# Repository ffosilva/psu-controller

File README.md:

# ATX Power Supply Controller (`psu-controller`)

[-brightgreen)](#pcb-layout--manufacturing-specs)

A discrete, analog hardware controller designed to sequence and manage standard ATX power supplies for non-standard motherboards, repurposed compute platforms (such as the AMD BC-250 mining board), single-board computers, and custom electronics fixtures.

---

## 📖 Table of Contents

- [Motivation & Problem Solved](#-motivation--problem-solved)
- [Key Features](#-key-features)
- [System Architecture](#-system-architecture)
- [Theory of Operation](#-theory-of-operation)
- [Header Pinout & Wiring](#-header-pinout--wiring)
- [Bill of Materials (BOM)](#-bill-of-materials-bom)
- [PCB Layout & Manufacturing Specs](#-pcb-layout--manufacturing-specs)
- [Bench Testing & Verification](#-bench-testing--verification)
- [Host BIOS Configuration](#-host-bios-configuration)
- [Repository Structure](#-repository-structure)
- [Documentation Index](#-documentation-index)
- [License](#-license)

---

## ⚡ Motivation & Problem Solved

Repurposed compute hardware (such as headless crypto-mining boards like the AMD BC-250, embedded industrial boards, and retro computing conversions) often lack standard front-panel ATX power management circuits. 

Without a dedicated controller:
1. **The Green Wire Hack:** Operators typically short the ATX `PS_ON#` wire (green) to Ground (black) with a jumper clip or switch.
2. **24/7 Power Waste & Wear:** The power supply and all chassis fans remain powered continuously at high wattage—even after the operating system cleanly halts and unmounts disks.
3. **Loss of ACPI Control:** Pressing a chassis button cannot trigger an ACPI graceful shutdown, risking filesystem corruption.

The **ATX Power Supply Controller** eliminates jumpers by providing an intelligent, fully autonomous, discrete hardware sequency bridge between any ATX power supply, the host motherboard, and your chassis buttons/LEDs.

---

## ✨ Key Features

- **Cold Boot RC Sequencing:** Momentary chassis button tap charges a timing capacitor ($C_{hold} = 22\ \mu\text{F}$ via $R_{bleed} = 120\text{ k}\Omega$), asserting ATX `PS_ON#` for ~3.5 seconds to allow the host to spin up.
- **Active Telemetry Latching:** Continuously monitors host power state via a 3.3V telemetry pin (e.g., TPM header pin `HOST_ON`). Once booted, host voltage locks `PS_ON#` low indefinitely.
- **Safe ACPI Button Mirroring:** Routes button pulses to the host's power button pad (`BTN_OUT`) through an open-drain N-channel MOSFET (`2N7000`), allowing:
  - **Short tap (200 ms):** Graceful OS ACPI shutdown without dropping ATX main power prematurely.
  - **Long press (4.0 seconds):** Hardware-level emergency forced power cut when OS kernel freezes.
- **Automated Standby Transition:** When the operating system finishes shutting down, `HOST_ON` drops to 0V. The controller de-asserts `PS_ON#` within 300 ms, putting the ATX power supply back into standby ($< 50\ \mu\text{A}$ quiescent draw).
- **Remote Microcontroller Wake (`ESP_WAKE`):** Accepts a 3.3V logic pulse from an ESP32, ESP8266, or Raspberry Pi Pico to power on the system remotely over WiFi/Bluetooth.
- **Hardware Remote Inhibit:** Uses an NPN transistor clamp to hardware-shunt `ESP_WAKE` directly to ground whenever the system is running, preventing accidental resets or wake loops.
- **Chassis Power LED Driver:** Built-in low-side switched driver (~15 mA) indicates true host system state.
- **100% Discrete Through-Hole Parts:** Built entirely with cheap, universally available "jellybean" components (TO-92 transistors, axial 1/4W resistors, DO-41 diodes, radial capacitors).
- **DIY Single-Sided PCB Design:** 1-layer bottom copper routing (`B.Cu` only, zero vias, zero top-side copper traces) designed specifically for home etching (toner transfer / photoresist) or desktop CNC milling.

---

## 🏗 System Architecture

```text
+---------------------+               +-----------------------+
|   Chassis Front     |               |    ATX Power Supply   |
|       Panel         |               |      (24-Pin Main)    |
|                     |               |                       |
| [Power Button]      |               |  Pin 9  (+5VSB, Purp) |
| [Power LED Ring]    |               |  Pin 16 (PS_ON#, Grn) |
|                     |               |  Pin 3  (GND, Blk)    |
+----------+----------+               +-----------+-----------+
           |                                      |
           | 4 wires                              | 3 wires
           v                                      v
     +-----+--------------------------------------+-----+
     |                                                  |
     |         ATX POWER SUPPLY CONTROLLER PCB          |
     |          (55 mm x 45 mm Single-Sided)            |
     |                                                  |
     +-----+--------------------------------------+-----+
           ^                                      ^
           | 2-3 wires                            | 2 wires
           |                                      |
+----------+----------+               +-----------+-----------+
| ESP32 / ESP8266     |               |   Host Motherboard    |
| Microcontroller     |               |     (AMD BC-250)      |
|                     |               |                       |
| - 5V / VIN (Power)  |               | - TPMS1 Pin 1 (3.3V)  |
| - WAKE (GPIO Out)   |               | - PWR_BTN# Solder Pad |
| - GND (Common)      |               | - Common Ground       |
+---------------------+               +-----------------------+
```

---

## 🔬 Theory of Operation

```text
========================================================================================
                          CIRCUIT SCHEMATIC OVERVIEW
========================================================================================

                                  +5VSB (J1 Pin 1, ATX Pin 9)
                                       |
                +----------------------+-------------------------------+
                |                      |                               |
            [R1: 10k]             Source [Q1: BS250]               [R_led: 330R]
                |                    (P-Ch MOSFET)                     |
  BTN_IN -------+------------------+ Gate                              v Anode
  (J3 Pin 1)    |                      | Drain                      [Power LED]
             [C_deb: 100nF]        [D2: 1N5819]                     (J4 Pin 1)
                |                      |                               | Cathode
  GND ----------+                      v                               (J4 Pin 2)
                                 Node [V_GATE]                         |
  HOST_ON (3.3V TPM) -----[D1: 1N5819]-+                               |
  (J2 Pin 1)                           |                               |
                                       |                               |
  ESP_WAKE (3.3V) ----[R5: 1k]---------+-----[D3: 1N5819]--+          |
  (J5 Pin 2)          |                                    |          |
                   Collector                               v          |
                      |                             +-------------+   |
  HOST_ON ---[R6: 10k]+ Base [Q5: 2N3904]           | [C_hold]    |   |
  (Inhibit)           | (Inhibit Switch)            | (22uF)      |   |
                   Emitter                          | [R_bleed]   |   |
                      |                             | (120k)      |   |
                     GND                            +------+------+   |
                                                           |          |
                                                          GND         |
                                                                    Gate
                                                                      v
                                                             +-----------------+
                                                             | Q2: 2N7000      |
                                ATX PS_ON# <-----------------+ (N-Ch MOSFET)   |
                                (J1 Pin 2, ATX Pin 16)       | Source          |
                                                             +--------+--------+
                                                                      |
                                                                     GND

  Q1 Drain (5V Pulse) --------[R2: 1k]-------------> Gate (Q3: 2N7000) -> BTN_OUT (J2.2)
  HOST_ON (3.3V TPM) ---------[R4: 4.7k]-----------> Base (Q4: 2N3904) -> LED- (J4.2)
========================================================================================
```

1. **Standby (Off):** ATX mains is plugged in. `+5VSB` is active. Node `V_GATE` is 0V, $Q_2$ is OFF, `PS_ON#` floats at 5V, power draw is $< 50\ \mu\text{A}$.
2. **Cold Power-On:** Pressing the chassis button pulls $Q_1$ gate low, turning $Q_1$ ON. A 5V pulse charges $C_{hold}$ ($22\ \mu\text{F}$) through Schottky diode $D_2$ in $< 2\text{ ms}$, immediately turning ON $Q_2$ and pulling `PS_ON#` to GND.
3. **Hold-Up Timer:** Once released, $C_{hold}$ discharges through $R_{bleed}$ ($120\text{ k}\Omega$). $Q_2$ remains fully saturated for ~3.5 seconds, giving the host ample time to power on and initialize.
4. **Active Latching:** As the host boots, its 3.3V TPM header asserts `HOST_ON`. Diode $D_1$ conducts, locking `V_GATE` to ~3.05V indefinitely.
5. **ACPI Button Mirroring:** While running, pressing the front panel button turns on $Q_3$, pulling the motherboard power pad (`BTN_OUT`) to ground. The OS registers the ACPI event and initiates a clean shutdown. `PS_ON#` stays grounded by `HOST_ON` during shutdown.
6. **Graceful Power Cut:** When the OS halts, the motherboard turns off and `HOST_ON` drops to 0V. $D_1$ stops conducting, $C_{hold}$ discharges in ~300 ms, $Q_2$ turns off, and the ATX supply turns off main rails.
7. **Emergency 4-Second Override:** If the OS freezes, holding the button for 4.0 seconds holds `BTN_OUT` low, triggering the motherboard hardware supervisor force-off.
8. **Remote Wake & Hardware Inhibit:** A 3.3V pulse on `ESP_WAKE` charges $C_{hold}$ via $D_3$, turning on the PSU. When the host is already running, $Q_5$ clamps the wake input directly to GND, preventing unexpected glitches.

---

## 🔌 Header Pinout & Wiring

| Header | Pin | Signal | Target Connection | Description |
| :--- | :--- | :--- | :--- | :--- |
| **J1: ATX PSU** | 1 | `+5VSB` | ATX 24-Pin Pin 9 (Purple) | Standby +5V DC power |
| | 2 | `PS_ON#` | ATX 24-Pin Pin 16 (Green) | Active-low main rail enable |
| | 3 | `GND` | ATX 24-Pin Pin 3/5/7/15/17 (Black) | Common system ground return |
| **J2: Host Board** | 1 | `HOST_ON` | Motherboard TPM Header Pin 1 (3.3V) | Active power telemetry sense line |
| | 2 | `BTN_OUT` | Motherboard `PWR_BTN#` Solder Pad | Open-drain ACPI button pulse output |
| **J3: Chassis Button**| 1 | `BTN_IN` | Pushbutton Terminal 1 | Momentary switch active-low input |
| | 2 | `GND` | Pushbutton Terminal 2 | Switch ground return |
| **J4: Power LED** | 1 | `LED+` | Power LED Anode (+) | +5V DC current-limited via onboard 330Ω |
| | 2 | `LED-` | Power LED Cathode (-) | Low-side switched ground via $Q_4$ |
| **J5: Remote MCU** | 1 | `+5VSB` | ESP32 `VIN` / `5V` | Standby power for external MCU |
| | 2 | `ESP_WAKE`| ESP32 GPIO (Output) | Remote wake active-high (3.3V) pulse |
| | 3 | `GND` | ESP32 `GND` | Shared ground return |

> [!TIP]
> Use an ATX 24-pin extension cable to tap Pin 9 (`+5VSB`), Pin 16 (`PS_ON#`), and Ground without altering or cutting your power supply harness.

For full pinouts, motherboard solder points, and step-by-step assembly advice, see [docs/wiring-guide.md](docs/wiring-guide.md).

---

## 📦 Bill of Materials (BOM)

All components are standard through-hole parts with wide global availability:

| Ref | Qty | Part / Value | Description | Package | Example MPN |
| :--- | :--- | :--- | :--- | :--- | :--- |
| **Q1** | 1 | BS250 | P-Channel Logic MOSFET (-45V, 180mA) | TO-92 | `BS250P` (or 2N3906 PNP) |
| **Q2, Q3** | 2 | 2N7000 | N-Channel Logic MOSFET (60V, 200mA) | TO-92 | `2N7000` |
| **Q4, Q5** | 2 | 2N3904 | NPN General Purpose BJT (40V, 200mA) | TO-92 | `2N3904` |
| **D1, D2, D3** | 3 | 1N5819 | Schottky Barrier Diode (40V, 1A, $V_F \approx 0.25\text{V}$) | DO-41 Axial | `1N5819` |
| **C_hold** | 1 | 22 µF, 25V | Radial Aluminum Electrolytic Capacitor | Radial Ø5mm | `ECA-1EHG220` |
| **C_deb, C_byp**| 2 | 100 nF (0.1 µF) | Multilayer Ceramic Capacitor (50V) | Radial 2.54mm | `C315C104K5R5TA` |
| **R1, R6** | 2 | 10 kΩ, 1/4W | Metal / Carbon Film Resistor (5%) | Axial 7.62mm | `CFR-25JB-52-10K` |
| **R2, R5** | 2 | 1 kΩ, 1/4W | Metal / Carbon Film Resistor (5%) | Axial 7.62mm | `CFR-25JB-52-1K` |
| **R4** | 1 | 4.7 kΩ, 1/4W | Metal / Carbon Film Resistor (5%) | Axial 7.62mm | `CFR-25JB-52-4K7` |
| **R_bleed** | 1 | 120 kΩ, 1/4W | Metal / Carbon Film Resistor (5%) | Axial 7.62mm | `CFR-25JB-52-120K` |
| **R_led** | 1 | 330 Ω, 1/4W | Metal / Carbon Film Resistor (5%) | Axial 7.62mm | `CFR-25JB-52-330R` |
| **J1, J5** | 2 | 3-Pin Header | 2.54mm (0.1") Male Pin Header | 1x03 THT | Standard 2.54mm Header |
| **J2, J3, J4** | 3 | 2-Pin Header | 2.54mm (0.1") Male Pin Header | 1x02 THT | Standard 2.54mm Header |

For detailed component substitutions, pinouts, and purchasing links, see [docs/bom.md](docs/bom.md).

---

## 🛠 PCB Layout & Manufacturing Specs

The PCB is built in KiCad 8 as a **true single-sided layout**:
- **Board Dimensions:** $55.0\text{ mm} \times 45.0\text{ mm}$
- **Layer Stackup:** 1-Layer Copper (`B.Cu` bottom solder side only). Zero copper traces on `F.Cu`, zero vias.
- **Top-Side Crossover Strategy:** Resistor `R2` ($10.16\text{ mm}$ axial span) and diode `D1` ($7.62\text{ mm}$ axial span) act as natural component bridges across bottom copper traces on `B.Cu`, avoiding the need for wire jumpers.
- **DIY Etch / Desktop CNC Milling Tolerances:**
  - Power / Ground Traces: `0.80 mm`
  - Signal Traces: `0.60 mm`
  - Minimum Copper Clearance: $\ge 0.45\text{ mm}$
  - Component Pads: `1.80 mm` outer diameter (`0.8 mm` drill)
  - Connector Pads: `2.00 mm` outer diameter (`1.0 mm` drill)
  - Expanded TO-92 Footprints: $\ge 2.54\text{ mm}$ lead spread for easy hand soldering and generous isolation.

### Manufacturing Files (`kicad/gerbers/`)
- `atx-psu-controller-B_Cu.gbr` — Bottom copper layer (traces & ground plane)
- `atx-psu-controller-B_Mask.gbr` — Solder mask (bottom)
- `atx-psu-controller-F_SilkS.gbr` — Top silkscreen (component placement & polarity)
- `atx-psu-controller-Edge_Cuts.gbr` — Board outline
- `atx-psu-controller-PTH.drl` — Excellon drill file (component holes only, no via drills)

---

## 🧪 Bench Testing & Verification

Before installing into your system, complete bench verification using a DC power supply and multimeter:

1. **Pre-Power Continuity Check:** Measure resistance between `+5VSB` and `GND` ($> 100\text{ k}\Omega$), and between `PS_ON#` and `GND` ($> 1\text{ M}\Omega$).
2. **Standby Current Draw:** Apply 5.0V to `J1.1`. Quiescent current must measure $< 50\ \mu\text{A}$ (typically $\sim 12\ \mu\text{A}$).
3. **Cold Boot Hold-Up Time:** Tap `BTN_IN` to `GND`. `PS_ON#` drops to $< 0.1\text{V}$ instantly and remains low for $2.5\text{s}$ to $3.5\text{s}$ before releasing.
4. **Telemetry Latch:** Apply 3.3V to `HOST_ON` within 2 seconds of button press. `PS_ON#` stays latched low indefinitely; the status LED lights up.
5. **ACPI Button Mirroring:** Tap `BTN_IN`. `BTN_OUT` pulses low ($< 0.1\text{V}$) while `PS_ON#` remains held low without interruption.
6. **Graceful Shutdown:** Remove 3.3V from `HOST_ON`. `PS_ON#` releases within 300 ms, and the LED turns off.
7. **Remote Wake & Inhibit:** 3.3V pulse on `ESP_WAKE` starts the PSU. When `HOST_ON` is 3.3V, `ESP_WAKE` is clamped to ground by $Q_5$.

For full testing protocols and verification logs, see [docs/testing.md](docs/testing.md).

---

## ⚙ Host BIOS Configuration

To take full advantage of automated cold-boot sequencing:
1. Enter your motherboard BIOS setup during boot (`DEL` or `F2`).
2. Go to **Advanced $\rightarrow$ ACPI Configuration / Power Management**.
3. Set **"Restore on AC Power Loss"** (or **"State After G3"**) to **`Power On`** (or **`Always On`**).
4. Save and exit (`F10`).

The host motherboard will now automatically boot the moment the ATX controller supplies +12V power!

---

## 📁 Repository Structure

```text
psu-controller/
├── docs/
│   ├── schematic.md         # Full ASCII schematic, netlist & circuit theory
│   ├── bom.md               # Complete Bill of Materials, footprints & substitutions
│   ├── wiring-guide.md      # Pinout, cable harnesses & motherboard solder points
│   ├── testing.md           # Bench test protocol, checklist & measurements
│   └── circuit-ideas.md     # Reference comparison (555 timers, flip-flops, latches)
├── kicad/
│   ├── atx-psu-controller.kicad_pro   # KiCad 8 project file
│   ├── atx-psu-controller.kicad_sch   # KiCad schematic
│   ├── atx-psu-controller.kicad_pcb   # KiCad single-sided PCB layout
│   └── gerbers/                       # Gerber RS-274X & Excellon drill files
├── openspec/
│   ├── config.yaml          # OpenSpec workspace configuration
│   ├── specs/               # Active system specifications
│   │   ├── atx-power-control/spec.md
│   │   └── pcb-layout/spec.md
│   └── changes/archive/     # Archived design proposals and implementation tasks
└── README.md                # Project documentation and user guide
```

---

## 📚 Documentation Index

- [Circuit Schematic & Netlist](docs/schematic.md)
- [Bill of Materials & Component Substitutions](docs/bom.md)
- [Hardware Wiring & Integration Guide](docs/wiring-guide.md)
- [Bench Testing & Verification Protocol](docs/testing.md)
- [Circuit Topology Research & Comparison](docs/circuit-ideas.md)
- [OpenSpec: ATX Power Control Spec](openspec/specs/atx-power-control/spec.md)
- [OpenSpec: PCB Layout Spec](openspec/specs/pcb-layout/spec.md)

---

## 📄 License

This hardware project is open-source and released under the [MIT License](LICENSE).

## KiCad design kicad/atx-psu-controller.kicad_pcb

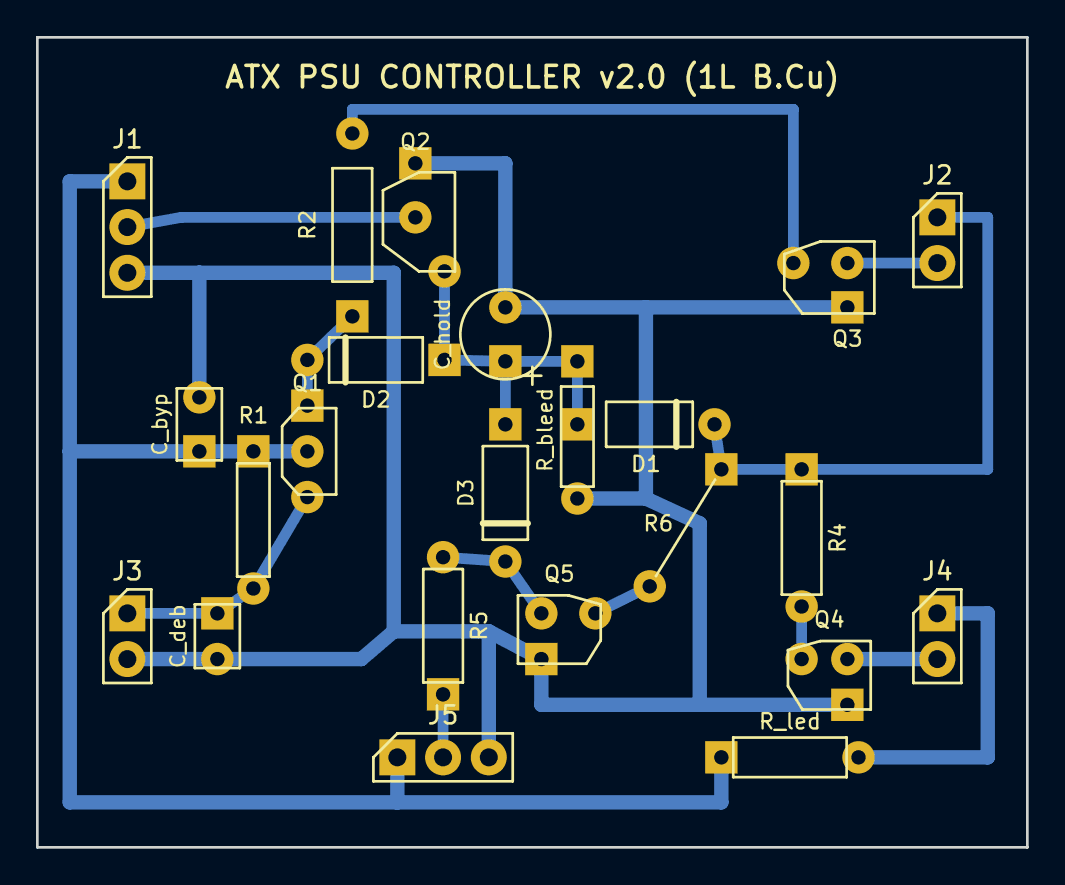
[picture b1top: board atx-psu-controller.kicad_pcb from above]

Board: 2 copper layers, 55.0 x 45.0 mm, 23 parts (0 on the bottom side), 15 nets.

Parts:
C_byp: 100nF; C_Disc_D5.0mm_W2.5mm_P2.54mm
C_deb: 100nF; C_Disc_D5.0mm_W2.5mm_P2.54mm
C_hold: 22uF; CP_Radial_D5.0mm_P2.50mm
D1, D2, D3: 1N5819; D_DO-41_SOD81_P7.62mm_Horizontal
J1: ATX_PSU; PinHeader_1x03_P2.54mm_Vertical
J2: HOST_BC250; PinHeader_1x02_P2.54mm_Vertical
J3: CHASSIS_BTN; PinHeader_1x02_P2.54mm_Vertical
J4: PWR_LED; PinHeader_1x02_P2.54mm_Vertical
J5: ESP_WAKE_HDR; PinHeader_1x03_P2.54mm_Vertical
Q1: BS250; TO-92_HandSolder
Q2, Q3: 2N7000; TO-92_HandSolder
Q4, Q5: 2N3904; TO-92_HandSolder
R1, R6: 10k; R_Axial_DIN0207_L6.3mm_D2.5mm_P7.62mm_Horizontal
R2, R5: 1k; R_Axial_DIN0207_L6.3mm_D2.5mm_P7.62mm_Horizontal
R4: 4.7k; R_Axial_DIN0207_L6.3mm_D2.5mm_P7.62mm_Horizontal
R_bleed: 120k; R_Axial_DIN0207_L6.3mm_D2.5mm_P7.62mm_Horizontal
R_led: 330R; R_Axial_DIN0207_L6.3mm_D2.5mm_P7.62mm_Horizontal

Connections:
+5VSB: C_byp.1, J1.1, J5.1, Q1.3, R1.1, R_led.1
BTN_IN: C_deb.1, J3.1, Q1.2, R1.2
BTN_OUT: J2.2, Q3.3
ESP_WAKE: J5.2, R5.1
GND: C_byp.2, C_deb.2, C_hold.2, J1.3, J3.2, J5.3, Q2.1, Q3.1, Q4.1, Q5.1, R_bleed.2
HOST_ON: D1.2, J2.1, R4.1, R6.1
LED+: J4.1, R_led.2
LED-: J4.2, Q4.3
N_ESP_CLAMP: D3.2, Q5.3, R5.2
N_Q3_G: Q3.2, R2.2
N_Q4_B: Q4.2, R4.2
N_Q5_B: Q5.2, R6.2
PS_ON#: J1.2, Q2.3
V_GATE: C_hold.1, D1.1, D2.1, D3.1, Q2.2, R_bleed.1
V_PULSE: D2.2, Q1.1, R2.1

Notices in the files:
README.md:
License: MIT
